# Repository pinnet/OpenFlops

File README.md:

# OpenFlops
OpenFlops is an Open Hardware Floppy Disk Drive emulator/simulator.

### Summary
From [Wikipedia](https://en.wikipedia.org/wiki/Floppy_disk_hardware_emulator):
> Older models of computers, electronic keyboards and industrial automation often used floppy disk drives for data transfer. Older equipment may be difficult to replace or upgrade because of cost, requirement for continuous availability or unavailable upgrades. Proper operation may require operating system, software and data to be read and written from and to floppies, forcing users to maintain floppy drives on supporting systems.

> Floppy disks and floppy drives are gradually going out of production, and replacement of malfunctioning drives, and the systems hosting them, is becoming increasingly difficult. Floppy disks themselves are fragile, or may need to be replaced often. An alternative is to use a floppy disk hardware emulator, a device which appears to be a standard floppy drive to the old equipment by interfacing directly to the floppy disk controller, while storing data in another medium such as a USB thumb drive, Secure Digital card, or a shared drive on a computer network. Emulators can also be used as a higher-performance replacement for mechanical floppy disk drives. 

OpenFlops is an Open Hardware implementation of such an emulator, inspired from the ubiquitous Gotek hardware. It is designed to run the [FlashFloppy](https://github.com/keirf/FlashFloppy) firmware, which gives it several improvements over the original Gotek:
- Can be installed on [many different platforms](https://github.com/keirf/FlashFloppy/wiki/Host-Platforms)
- Directly supports a [wide range of image formats](https://github.com/keirf/FlashFloppy/wiki/Image-Formats)
- [Flexible track layout](https://github.com/keirf/FlashFloppy/wiki/Track-Layouts) for Raw Sector Images
- [Extremely configurable](https://github.com/keirf/FlashFloppy/wiki/FF.CFG-Configuration-File)
- Supports [AutoSwap](https://github.com/keirf/FF_AutoSwap) for games with a large number of disks
- Easily accessible pin headers for connection of a [i2c display](https://github.com/keirf/FlashFloppy/wiki/Hardware-Mods#lcd-display) (either OLED or LCD), [rotary encoder](https://github.com/keirf/FlashFloppy/wiki/Hardware-Mods#rotary-encoder) (including power)
- Built-in amplified speaker, or easily-accessible pin header for an external one
- USB connector can either be soldered on the board or connected to a pin header
- Connected Motor signal
- Emulates two drives at the same time (Not yet supported by the firmware, but [it will come](https://github.com/keirf/FlashFloppy/wiki/Donations))
- Has additional 3.3V, 5V and GND power pins
- And hey, it's Open Hardware!

All of this comes in the same form factor (and mounting holes) as the board installed in the original Gotek, hence it can be easily installed in any shell or enclosure designed for it.

### Assembly and Installation
Solder all components to the board. I suggest starting with the main microcontroller (U3), as it uses an LQFP package which is tricky to solder: the recommended technique is drag soldering, there are many videos about that on YouTube, so please look there for advice. I recommend soldering the bare minimum components needed for programming and then trying to flash it right away. This way you will be able to fix your soldering without too many components getting in the way, if needed. You will need a USB/TTL Serial converter for this: one with 3.3V I/O level is recommended, but a 5V one can be used, too (most pins on STM32 microcontrollers are 5V-tolerant, so don't worry, it's not a bad hack!). You shouldn't pay more than 1-2€ for it in any case, anyway. So, when you are ready:

- Solder U3, Y1, C3 and C5, then the programming header (the top one with power, BOOT0, TX, RX, etc.)
- Check for shorts on the 3.3V power lines, you can easily do this on the pads for C6-C10
- If your USB/Serial adapter has a 3.3V output, connect it to 3.3V on the power header, then connect ground, RX and TX
- If no 3.3V output is available, solder U4 and power the board through the 5V pin on the power header

Now you should be able to [program the STM32 microcontroller](https://github.com/keirf/FlashFloppy/wiki/Firmware-Programming). If you have difficultes you can try adding R10 (and C4) and maybe a few of C6-C10, but most likely the problem will be with the solder joints on U3, as soldering this kind of package manually is never easy, so please get a lens (or even better, a microscope) and double-check your job.

The serial adapter is only necessary for the first flashing. Subsequent updates [can be done easily via USB](https://github.com/keirf/FlashFloppy/wiki/Firmware-Update).

Note that most components are necessary, but there are a few you can skip if you are feeling lazy:
- If you are not interested in the head movement sound, you can skip the following components: SPK1, D2, R5, R6, Q7.
- If your LCD/OLED display already has pull-up resistors for the SDA/SCK lines (most do), you can skip R3 and R4.

### Configuration
Please refer to the FlashFloppy wiki for the [initial setup](https://github.com/keirf/FlashFloppy/wiki/Initial-Setup) and an overview of the [available configuration options](https://github.com/keirf/FlashFloppy/wiki/FF.CFG-Configuration-File).

Some options that you will want to override the default values of, in order to take advantage of all the features OpenFlops provides, are the following:
- `motor-delay`
- `rotary`
- `display-type`

### Releases
If you want to get this board produced, you are recommended to get [the latest release](https://github.com/SukkoPera/OpenFlops/releases) rather than the current git version, as the latter might be under development and is not guaranteed to be working.

Every release is accompanied by its Bill Of Materials (BOM) file and any relevant notes about it, which you are recommended to read carefully.

### License
The OpenFlops documentation, including the design itself, is copyright &copy; SukkoPera 2019-2020.

OpenFlops is Open Hardware licensed under the [CERN OHL v. 1.2](http://ohwr.org/cernohl).

You may redistribute and modify this documentation under the terms of the CERN OHL v.1.2. This documentation is distributed *as is* and WITHOUT ANY EXPRESS OR IMPLIED WARRANTIES whatsoever with respect to its functionality, operability or use, including, without limitation, any implied warranties OF MERCHANTABILITY, SATISFACTORY QUALITY, FITNESS FOR A PARTICULAR PURPOSE or infringement. We expressly disclaim any liability whatsoever for any direct, indirect, consequential, incidental or special damages, including, without limitation, lost revenues, lost profits, losses resulting from business interruption or loss of data, regardless of the form of action or legal theory under which the liability may be asserted, even if advised of the possibility or likelihood of such damages.

A copy of the full license is included in file [LICENSE.pdf](LICENSE.pdf), please refer to it for applicable conditions. In order to properly deal with its terms, please see file [LICENSE_HOWTO.pdf](LICENSE_HOWTO.pdf).

The contact points for information about manufactured Products (see section 4.2) are listed in file [PRODUCT.md](PRODUCT.md).

Any modifications made by Licensees (see section 3.4.b) shall be recorded in file [CHANGES.md](CHANGES.md).

The Documentation Location of the original project is https://github.com/SukkoPera/OpenFlops/.

### Support the Project
Since the project is open you are free to get the PCBs made by your preferred manufacturer, however in case you want to support the development, you can order them from PCBWay through this link:

You get my gratitude and cheap, professionally-made and good quality PCBs, I get some credit that will help with this and [other projects](https://www.pcbway.com/project/member/shareproject/?bmbid=41100). You won't even have to worry about the various PCB options, it's all pre-configured for you!

Also, if you still have to register to that site, [you can use this link](https://www.pcbway.com/setinvite.aspx?inviteid=41100) to get some bonus initial credit (and yield me some more).

Again, if you want to use another manufacturer, feel free to, don't feel obligated :). But then you can buy me a coffee if you want:

### Get Help
If you need help or have questions, you can join [the official Telegram group](https://t.me/joinchat/HUHdWBC9J9JnYIrvTYfZmg).

### Thanks
- H.M for publishing the [original Gotek schematics](doc/gotek_usb-fde_block-diagram.jpg)
- [keirf](https://github.com/keirf) for FlashFloppy
- Brian Allan for suggesting some improvements for the Speaker circuit
- Ray Bellis for suggesting adding pin headers for the USB port and speaker
- Mario Babeu for suggesting to line up the orientation of LD1 and LD2
- Patrick Kerkhof for sending me a lot of original Gotek housing for dimensional testing

# OpenFlopsXT
A remix smaller pcb with support of flashfloppy extensions and a 24pin flat flex connector for a breakout display board that supports SD cards and should fit an Amiga A500 in a mezzanine configuration. This is a work in progress and has not been proven

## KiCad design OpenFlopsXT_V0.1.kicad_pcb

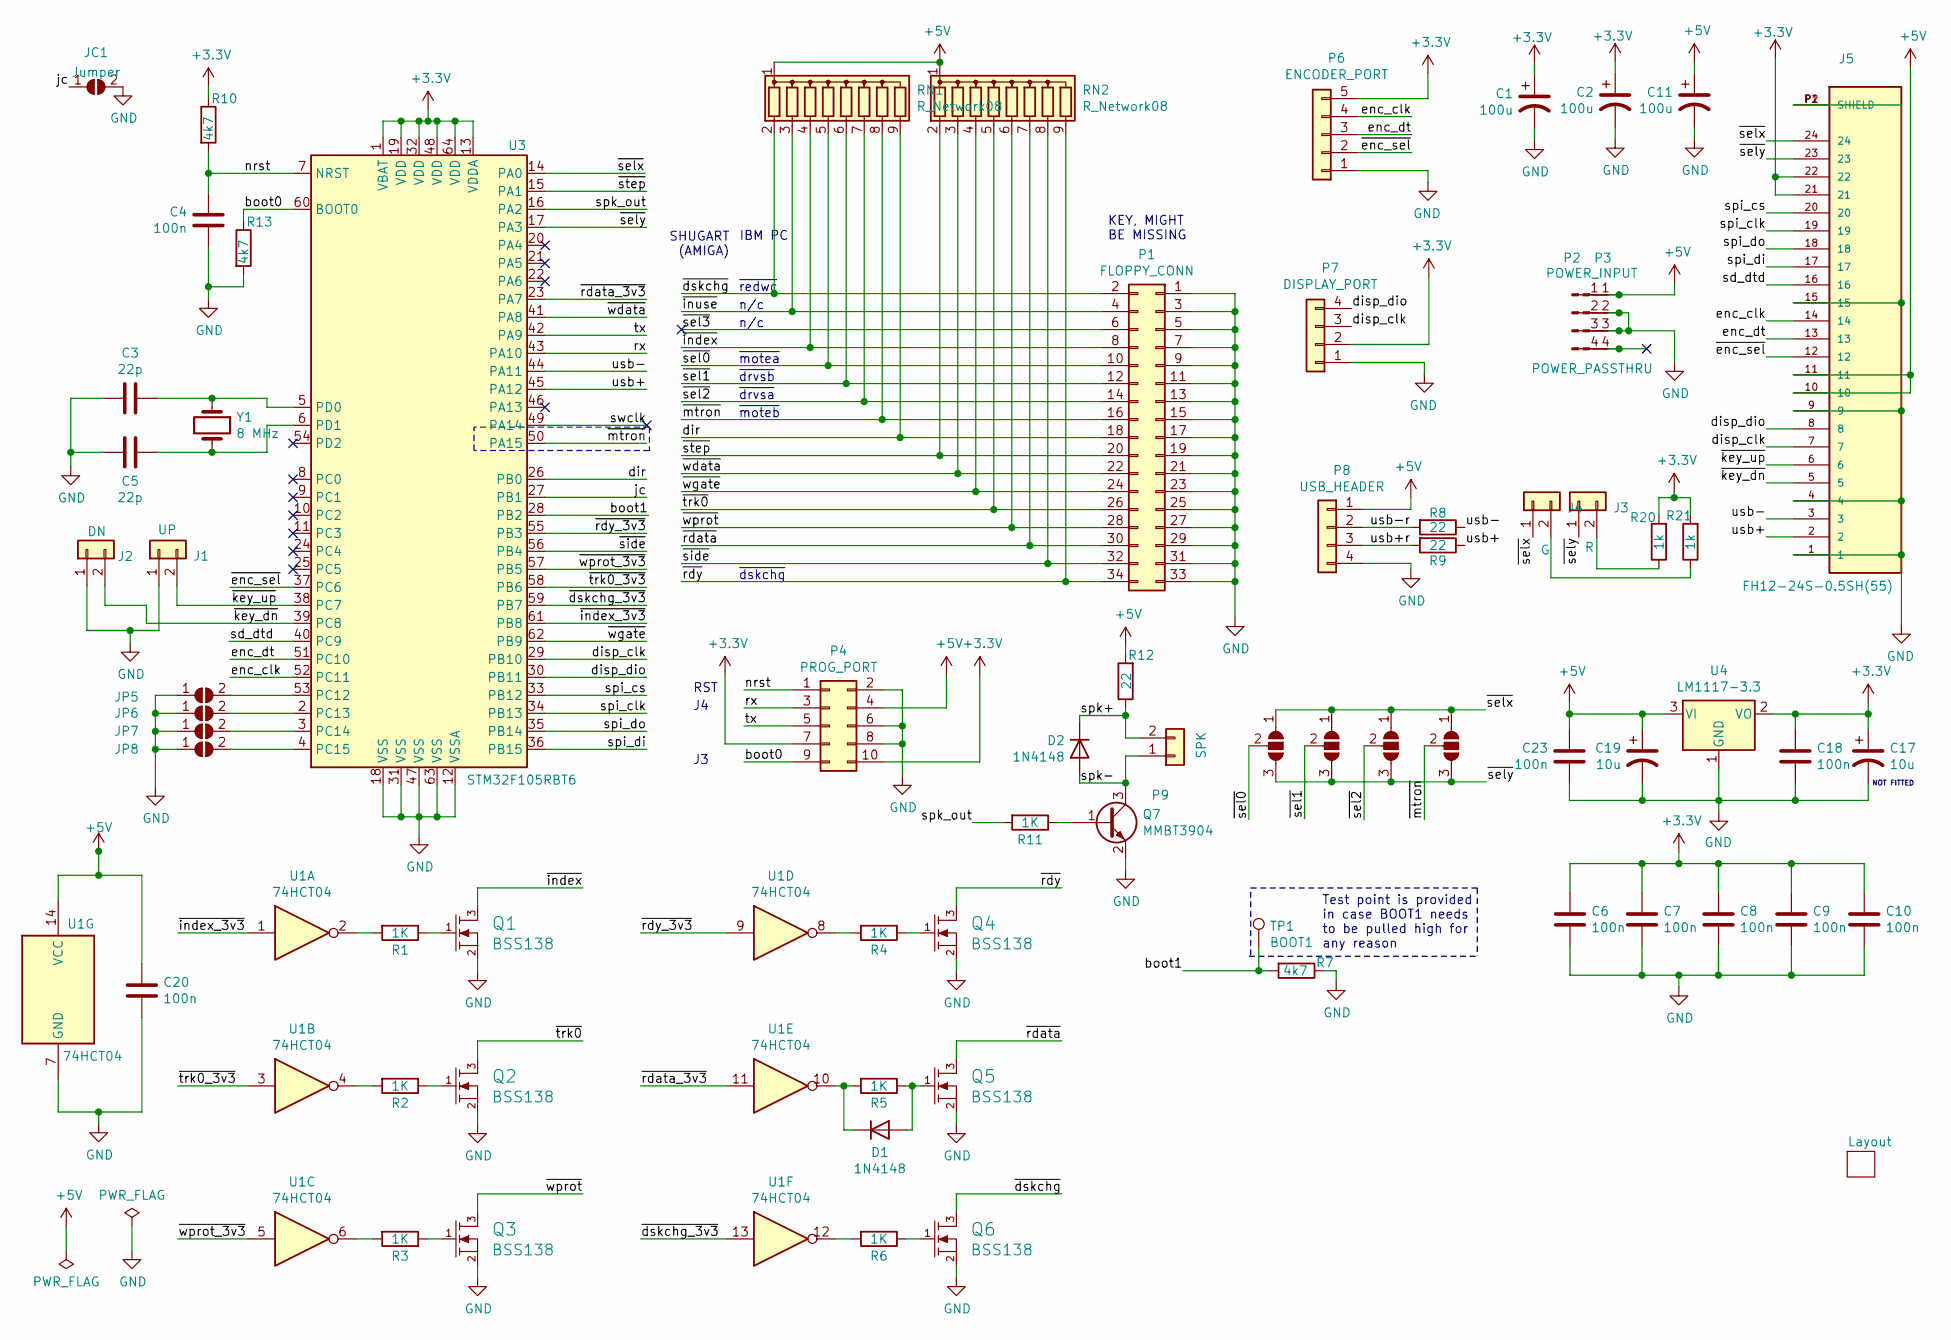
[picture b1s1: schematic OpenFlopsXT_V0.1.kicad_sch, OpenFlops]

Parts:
C1: 100u; SolderJumper-2_P1.3mm_Open_RoundedPad1.0x1.5mm
C2, C11: 100u; CP_Radial_D6.3mm_P2.50mm
C3, C5: 22p; C_0805_2012Metric_Pad1.15x1.40mm_HandSolder; MFG Part Num MULTILAYER CERAMIC CAPACITORS MLCC - SM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; JLCPCB PN CL21C220JBANNNC
C4, C6, C7, C8, C9, C10, C18, C20, C23: 100n; C_0805_2012Metric_Pad1.15x1.40mm_HandSolder; MFG Part Num MULTILAYER CERAMIC CAPACITORS MLCC - SM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; JLCPCB PN CC0805KRX7R9BB104
C17, C19: 10u; CP_Radial_D6.3mm_P2.50mm
D1, D2: 1N4148; D_SOD-323_HandSoldering; MFG Part Num SWITCHING DIODE 100V 150MA 1.25V @ 150M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; JLCPCB PN 1N4148WS
J1: UP; PinHeader_1x02_P2.54mm_Mute
J2: DN; PinHeader_1x02_P2.54mm_Mute
J3: R; PinHeader_1x02_P2.54mm_Mute
J4: G; PinHeader_1x02_P2.54mm_Mute
J5: FH12-24S-0.5SH(55); HRS_FH12-24S-0.5SH(55)
JC1: Jumper; SolderJumper-2_P1.3mm_Open_RoundedPad1.0x1.5mm
JP1: SEL0; SolderJumper-3_P1.3mm_Open_RoundedPad1.0x1.5mm
JP2: SEL1; SolderJumper-3_P1.3mm_Open_RoundedPad1.0x1.5mm
JP3: SEL2; SolderJumper-3_P1.3mm_Open_RoundedPad1.0x1.5mm
JP4: MO; SolderJumper-3_P1.3mm_Open_RoundedPad1.0x1.5mm
JP5, JP6, JP7, JP8: SolderJumper_2_Open; SolderJumper-2_P1.3mm_Open_RoundedPad1.0x1.5mm
P1: FLOPPY_CONN; PinHeader_2x17_P2.54mm_Vertical
P2: POWER_INPUT; PinHeader_1x04_P2.54mm_Vertical_Power
P3: POWER_PASSTHRU; PinHeader_1x04_P2.54mm_Vertical_Power
P4: PROG_PORT; PinHeader_2x05_P2.54mm_Vertical
P6: ENCODER_PORT; PinHeader_1x05_P2.54mm_Vertical
P7: DISPLAY_PORT; PinHeader_1x04_P2.54mm_Vertical
P8: USB_HEADER; PinHeader_1x04_P2.54mm_Vertical
P9: SPK; PinHeader_1x02_P2.54mm_Mute
Q1, Q2, Q3, Q4, Q5, Q6: BSS138; SOT-23_Handsoldering; MFG Part Num MOSFET N TRENCH 50V 220MA 1.5V @ 1MA 3.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; JLCPCB PN BSS138
Q7: MMBT3904; SOT-23_Handsoldering; MFG Part Num TRANSISTORS (NPN/PNP) NPN 200MA 40V SOT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; JLCPCB PN MMBT3904
R1, R2, R3, R4, R5, R6: 1K; R_0805_2012Metric_Pad1.15x1.40mm_HandSolder; MFG Part Num CHIP RESISTOR - SURFACE MOUNT 1KOHMS ±1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; JLCPCB PN 0805W8F1001T5E
R7, R10, R13: 4k7; R_0805_2012Metric_Pad1.15x1.40mm_HandSolder; MFG Part Num CHIP RESISTOR - SURFACE MOUNT 4.7KOHMS 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; JLCPCB PN 0805W8F4701T5E
R8, R9, R12: 22; R_0805_2012Metric_Pad1.15x1.40mm_HandSolder; MFG Part Num CHIP RESISTOR - SURFACE MOUNT 22OHMS ±1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; JLCPCB PN 0805W8F220JT5E
R11: 1K; R_0805_2012Metric_Pad1.15x1.40mm_HandSolder
R20, R21: 1k; R_0805_2012Metric_Pad1.15x1.40mm_HandSolder
RN1, RN2: R_Network08; R_Array_SIP9
TP1: BOOT1; TestPoint_Pad_D1.0mm
U1: 74HCT04; SOIC-14_3.9x8.7mm_P1.27mm; MFG Part Num GATES AND INVERTERS SOIC-14_150MIL ROHS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; JLCPCB PN 74HCT04D
U3: STM32F105RBT6; LQFP-64_Handsoldering; MFG Part Num ST MICROELECTRONICS LQFP-64_10X10X05P R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; JLCPCB PN STM32F105RBT6
U4: LM1117-3.3; SOT-223-3_TabPin2; MFG Part Num LOW DROPOUT REGULATORS(LDO) POSITIVE FI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; JLCPCB PN AMS1117-3.3
Y1: 8 MHz; Crystal_HC49-U_Vertical

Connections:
+3V3: C1.1, C2.1, C6.1, C7.1, C8.1, C9.1, C10.1, C17.1, C18.1, J5.21, J5.22, P4.7, P4.10, P6.5, P7.2, R10.1, R20.2, R21.2, U3.1 (VBAT), U3.13 (VDDA), U3.19 (VDD), U3.32 (VDD), U3.48 (VDD), U3.64 (VDD), U4.2 (VO)
+5V: C11.1, C19.1, C20.1, C23.1, J5.10, J5.11, P2.1, P3.1, P4.4, P8.1, R12.2, RN1.1 (common), RN2.1 (common), U1.14 (VCC), U4.3 (VI)
/boot0: P4.9, R13.1, U3.60 (BOOT0)
/boot1: R7.2, TP1.1, U3.28 (PB2)
/dir: P1.18, RN1.9 (R8), U3.26 (PB0)
/disp_clk: J5.7, P7.3, U3.29 (PB10)
/disp_dio: J5.8, P7.4, U3.30 (PB11)
/enc_clk: J5.14, P6.4, U3.52 (PC11)
/enc_dt: J5.13, P6.3, U3.51 (PC10)
/jc: JC1.1 (A), U3.27 (PB1)
/nrst: C4.1, P4.1, R10.2, U3.7 (NRST)
/rx: P4.3, U3.43 (PA10)
/sd_dtd: J5.16, U3.40 (PC9)
/spi_clk: J5.19, U3.34 (PB13)
/spi_cs: J5.20, U3.33 (PB12)
/spi_di: J5.17, U3.36 (PB15)
/spi_do: J5.18, U3.35 (PB14)
/spk+: D2.1 (K), P9.2, R12.1
/spk-: D2.2 (A), P9.1, Q7.3 (C)
/spk_out: R11.2, U3.16 (PA2)
/swclk: U3.49 (PA14)
/tx: P4.5, U3.42 (PA9)
/usb+: J5.2, R9.1, U3.45 (PA12)
/usb+r: P8.3, R9.2
/usb-: J5.3, R8.1, U3.44 (PA11)
/usb-r: P8.2, R8.2
/~dskchg_3v3: U1.13, U3.59 (PB7)
/~dskchg: P1.2, Q6.3 (D), RN1.2 (R1)
/~enc_sel: J5.12, P6.2, U3.37 (PC6)
/~index_3v3: U1.1, U3.61 (PB8)
/~index: P1.8, Q1.3 (D), RN1.4 (R3)
/~inuse: P1.4, RN1.3 (R2)
/~key_dn: J2.2, J5.5, U3.39 (PC8)
/~key_up: J1.2, J5.6, U3.38 (PC7)
/~mtron: JP4.2 (C), P1.16, RN1.8 (R7), U3.50 (PA15)
/~rdata_3v3: U1.11, U3.23 (PA7)
/~rdata: P1.30, Q5.3 (D), RN2.7 (R6)
/~rdy_3v3: U1.9, U3.55 (PB3)
/~rdy: P1.34, Q4.3 (D), RN2.9 (R8)
/~sel0: JP1.2 (C), P1.10, RN1.5 (R4)
/~sel1: JP2.2 (C), P1.12, RN1.6 (R5)
/~sel2: JP3.2 (C), P1.14, RN1.7 (R6)
/~sel3: P1.6
/~selx: J4.1, J5.24, JP1.1 (A), JP2.1 (A), JP3.1 (A), JP4.1 (A), U3.14 (PA0)
/~sely: J3.1, J5.23, JP1.3 (B), JP2.3 (B), JP3.3 (B), JP4.3 (B), U3.17 (PA3)
/~side: P1.32, RN2.8 (R7), U3.56 (PB4)
/~step: P1.20, RN2.2 (R1), U3.15 (PA1)
/~trk0_3v3: U1.3, U3.58 (PB6)
/~trk0: P1.26, Q2.3 (D), RN2.5 (R4)
/~wdata: P1.22, RN2.3 (R2), U3.41 (PA8)
/~wgate: P1.24, RN2.4 (R3), U3.62 (PB9)
/~wprot_3v3: U1.5, U3.57 (PB5)
/~wprot: P1.28, Q3.3 (D), RN2.6 (R5)
GND: C1.2, C2.2, C3.2, C4.2, C5.2, C6.2, C7.2, C8.2, C9.2, C10.2, C11.2, C17.2, C18.2, C19.2, C20.2, C23.2, J1.1, J2.1, J5.1, J5.4, J5.9, J5.15, J5.P1 (SHIELD), J5.P2 (SHIELD), JC1.2 (B), JP5.1 (A), JP6.1 (A), JP7.1 (A), JP8.1 (A), P1.1, P1.3, P1.5, P1.7, P1.9, P1.11, P1.13, P1.15, P1.17, P1.19, P1.21, P1.23, P1.25, P1.27, P1.29, P1.31, P1.33, P2.2, P2.3, P3.2, P3.3, P4.2, P4.6, P4.8, P6.1, P7.1, P8.4, Q1.2 (S), Q2.2 (S), Q3.2 (S), Q4.2 (S), Q5.2 (S), Q6.2 (S), Q7.2 (E), R7.1, R13.2, U1.7 (GND), U3.12 (VSSA), U3.18 (VSS), U3.31 (VSS), U3.47 (VSS), U3.63 (VSS), U4.1 (GND); also elsewhere on the board
unnamed: C3.1, U3.5 (PD0), Y1.1
unnamed: C5.1, U3.6 (PD1), Y1.2
unnamed: D1.1 (K), R5.2, U1.10
unnamed: D1.2 (A), Q5.1 (G), R5.1
unnamed: J3.2, R20.1
unnamed: J4.2, R21.1
unnamed: JP5.2 (B), U3.53 (PC12)
unnamed: JP6.2 (B), U3.2 (PC13)
unnamed: JP7.2 (B), U3.3 (PC14)
unnamed: JP8.2 (B), U3.4 (PC15)
unnamed: P2.4, P3.4
unnamed: Q1.1 (G), R1.1
unnamed: Q2.1 (G), R2.1
unnamed: Q3.1 (G), R3.1
unnamed: Q4.1 (G), R4.1
unnamed: Q6.1 (G), R6.1
unnamed: Q7.1 (B), R11.1
unnamed: R1.2, U1.2
unnamed: R2.2, U1.4
unnamed: R3.2, U1.6
unnamed: R4.2, U1.8
unnamed: R6.2, U1.12

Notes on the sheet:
RST
SHUGART (AMIGA)
~{redwc}
n/c
~{motea}
~{drvsb}
~{drvsa}
~{moteb}
~{dskchg}
IBM PC
KEY, MIGHT BE MISSING
Test point is provided in case BOOT1 needs to be pulled high for any reason
NOT FITTED

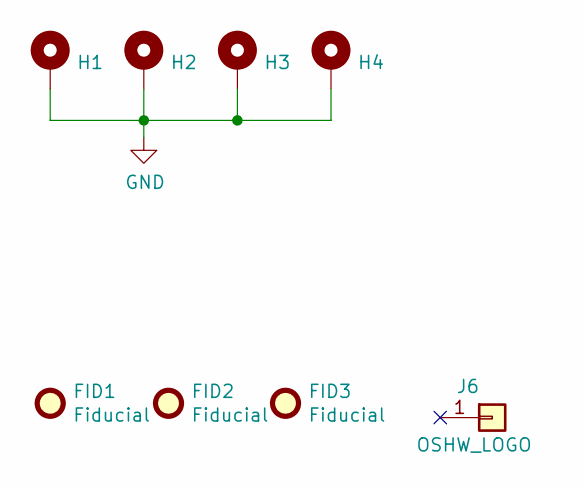
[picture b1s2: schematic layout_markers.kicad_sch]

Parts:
FID1, FID2, FID3: Fiducial; Fiducial_0.75mm_Mask1.5mm
H1, H2, H3, H4: MountingHole_Pad; MountingHole_M3_Pad
J6: OSHW_LOGO; OSHW-Logo2_9.8x8mm_Copper

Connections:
GND: H1.1, H2.1, H3.1, H4.1; also elsewhere on the board

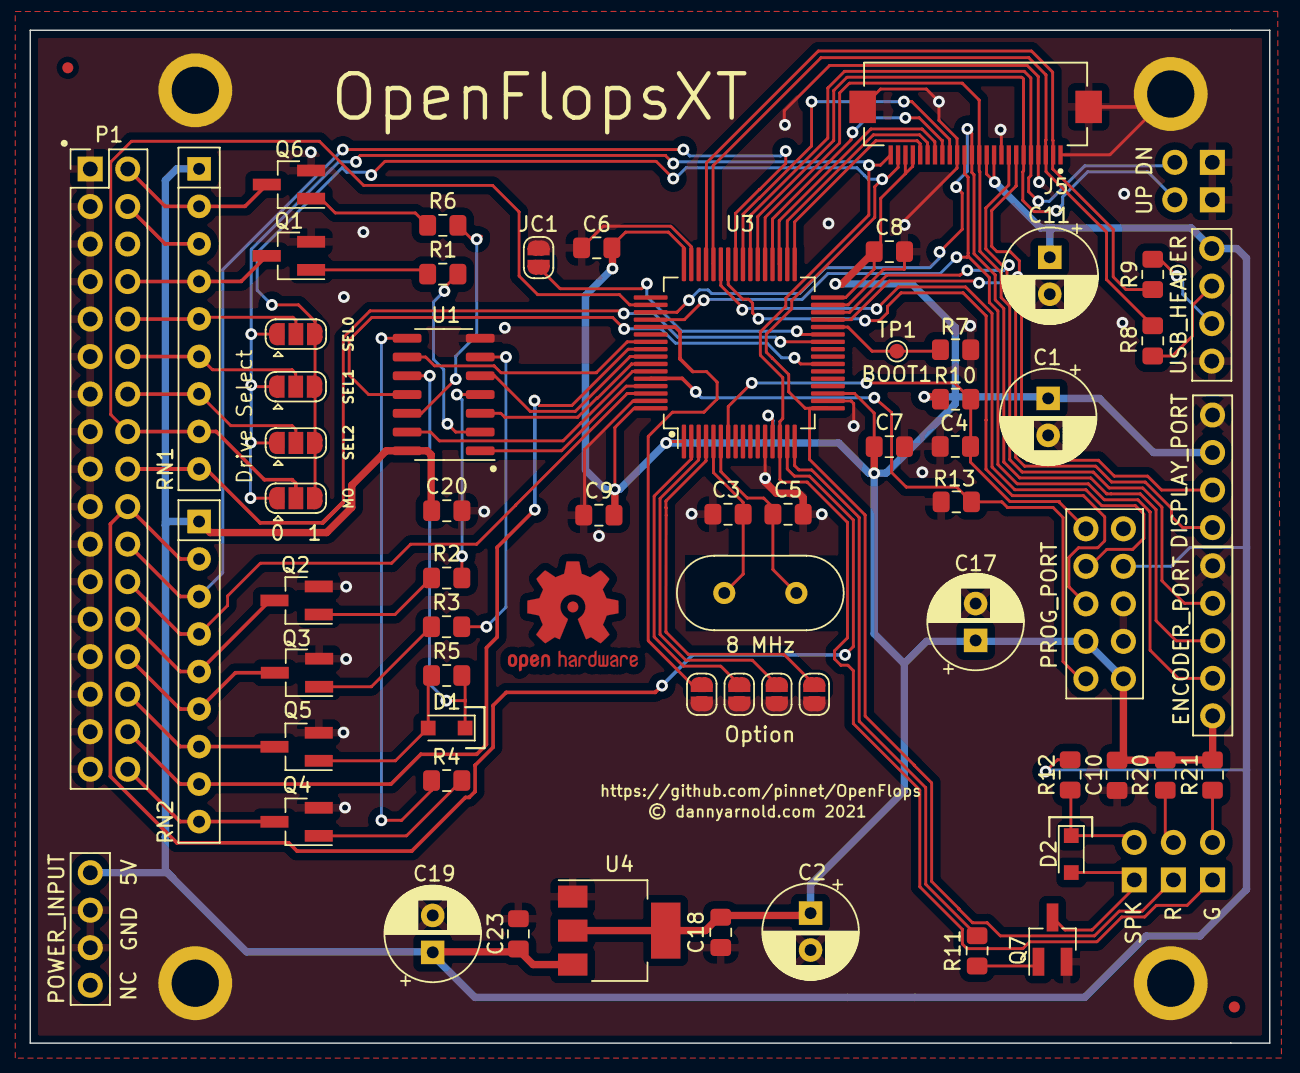
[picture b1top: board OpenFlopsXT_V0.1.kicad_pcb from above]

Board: 2 copper layers, 83.9 x 68.6 mm, 76 parts (0 on the bottom side), 73 nets.

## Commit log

2021-08-09 Added Cost Reduced version
2021-08-18 OpenFlopsXT initial commit
2021-08-18 Corrected Github URL
2021-08-18 Fixed DRC on OpenFlopsXT
2021-08-18 Upgraded Flat Flex Connector OpenFlopsXT
2021-08-18 Added 3d images of OpenFlopsXT
2021-08-18 Updated Readme to add OpenFlopsXT addendum
2021-08-18 Quick edit readme
2021-08-18 fixed typo Readme
2021-08-24 Tidy up OpenFlopsXT for manufature
2021-08-24 Correct missing pin 1 locators and Tidy up OpenfFLopsXT
2021-08-24 Retreve from backup due to git error
2021-08-24 Cleanup and fix silkscreen isue. OpenFlopsXT

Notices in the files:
OpenFlopsXT_V0.1.kicad_pcb:
© dannyarnold.com 2021
OpenFlopsXT_V0.1.kicad_sch:
Licensed under CERN OHL v.1.2
